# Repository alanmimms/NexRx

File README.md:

# NexRx: Open-Source Ham Radio SDR Receiver System
## Overview & Core Concepts

### What is NexRx?

NexRx is an ambitious open-source project that reimagines how we
interact with ham radio receivers. Instead of the knobs, buttons,
and menu diving that have defined radio interfaces for decades, NexRx
presents a browser-based interface built around a revolutionary
concept called "setboxes."

Think of it as bringing ham radio into the modern computing age -
where your radio's interface is as flexible and powerful as the
software on your computer, but still maintains the real-time
performance demands of RF communication.

This is an overview of the project. There is much more in the `./doc`
directory.

The entire project uses the MIT License, covering everything from
hardware designs and PCB layouts to software source code. This isn't
just another commercial radio with a fancy display - it's a
community-driven platform designed to push ham radio technology
forward for everyone.

### The Big Idea: Setboxes

Here's where NexRx gets interesting. Traditional radios force you to
think in terms of physical controls - turn this knob for frequency,
press that button for mode, flip this switch for antenna selection.
But why should software-defined radio be limited by the metaphors of
analog hardware?

NexRx introduces "setboxes" - think of them as smart presets that can
inherit settings from each other, just like object-oriented
programming. Instead of having separate "band" and "mode" controls,
you might have a setbox called "40m-CW-Contest" that inherits basic
40-meter settings from a parent "40m" setbox, adds CW-specific
parameters from a "CW" setbox, and then layers on contest-specific
configurations.

```mermaid
graph TD
    A[Global Settings] --> B[40m Band]
    A --> C[CW Mode]
    A --> D[Contest Setup]
    B --> E[40m-CW-Contest]
    C --> E
    D --> E
    
    style A fill:#e1f5fe
    style E fill:#c8e6c9
```

This hierarchy means you can set your antenna preferences once in
"Global Settings," define band-specific power levels in "40m Band,"
configure CW tone preferences in "CW Mode," and create
contest-specific memory channels in "Contest Setup." When you activate
"40m-CW-Contest," it automatically combines all these inherited
settings with any overrides you've defined specifically for that
configuration.

### Why This Matters

Traditional radio interfaces suffer from what we might call "control
soup" - every setting lives at the same level, making it hard to
organize your preferences logically. Want to use different antennas
for 160m versus other bands? You'll be manually switching antennas
every time you change bands. Prefer different power levels for CW
versus SSB? Hope you remember to adjust that knob every time you
change modes.

Setboxes solve this by letting you organize your radio's behavior
hierarchically. Set up your preferences once, then let the inheritance
system handle the details. The result is a radio that adapts to your
operating style instead of forcing you to adapt to its limitations.

### System Overview

NexRx consists of three main components that work together
seamlessly:

**Hardware Platform**: Built around an STM32H753 microcontroller
running at 480MHz with a full megabyte each of flash and RAM. This
isn't your typical Arduino project - we're talking serious
computational power running Zephyr RTOS. The RF hardware handles general
HF coverage from 1MHz to 30MHz.

**Embedded Software**: Written in modern C++20, this handles the
real-time RF control, basic DSP processing, and serves as a web
server. It presents itself to your computer as USB, so there's no
driver installation or network configuration hassles.

**Native Application**: This is where the magic happens. Using a
modern framework (TBD) this app runs on Linux, MacOS, and even Windows
on 64-bit PC or ARM. It handles advanced DSP, the setbox management
system, and provides rich visualizations like waterfall displays and
spectrum analysis. The interface runs entirely on the PC. The NexRx
hardware is essentially "headless".

The beauty of this architecture is its simplicity from the user's
perspective. Plug in the USB cable, install the app, and you're ready
to operate. But under the hood, you have access to computational power
and interface flexibility that would be impossible with traditional
radio architectures.

### Key Design Principles

**Inheritance Over Configuration**: Rather than configuring every
parameter for every situation, set up logical hierarchies and let
inheritance handle the complexity. Your "DX" setbox can inherit from
your "20m" setbox, which inherits from your "HF" setbox, which
inherits from your global preferences.

**Native Interface**: No drivers to manage, no compatibility worries
across different operating systems.

**Community-Driven Development**: The entire project is open source
with permissive licensing specifically to encourage community
contributions, modifications, and improvements. This is ham radio,
after all - we're supposed to be experimenting and learning.

**Real-Time Performance**: Despite the web-based interface, NexRx
maintains the real-time performance requirements of RF operation
through careful architecture and efficient protocols.

### The Vision

NexRx isn't just another SDR project - it's an attempt to demonstrate
what ham radio interfaces could become if we stopped thinking in terms
of analog radio metaphors and started thinking in terms of modern
software design patterns.

Imagine having complete recordings of every QSO with automatic digital
mode decoding, multiple simultaneous receive frequencies with
independent waterfalls, or antenna switching that automatically adapts
to your operating patterns. These capabilities become natural
extensions of the setbox paradigm rather than complex features bolted
onto traditional radio designs.

The goal is to create a platform that grows with you as an operator,
adapts to your preferences, and provides the kind of deep
configurability that makes ham radio uniquely satisfying - but without
the traditional complexity that makes advanced features intimidating
to explore.

# MCP Server

To create the Gemini MCP server I use for Kicad collaboration, you
have to add something like the following to your
`~/.gemini/settings.json` file:

	{

	...

	  "mcpServers": {
		"NexRxMCP": {
		  "command": "/home/yourusername/NexRx/.venv/bin/python3",
		  "args": ["/home/yourusername/NexRx/tools/mcp-server.py"],
		  "trust": true
		}
	  }
	}

# Building the gateware, firmware, and software

To do a top-level single-command build run `./build.sh` (or `cmake -B
build && cmake --build build`). This orchestrates all components and
generates the complete tree in build/:

  * `zephyr.bin`
  * `top.bin`
  * `build/app/nexrx-app`
  * `build/twin/nexrx-signalgen`

To iterate on a given subdirectory, you can repeatedly build just that
subdirectory's components by `cd` *subdir* `&& ./build.sh`.

  * `cd fw && ./build.sh` -> outputs to `fw/build/zephyr/`
  * `cd CPLD && ./build.sh` -> outputs to `CPLD/build/`
  * `cd app && ./build.sh` -> outputs to `app/build/`
  * `cd twin && ./build.sh` -> outputs to `twin/build/`

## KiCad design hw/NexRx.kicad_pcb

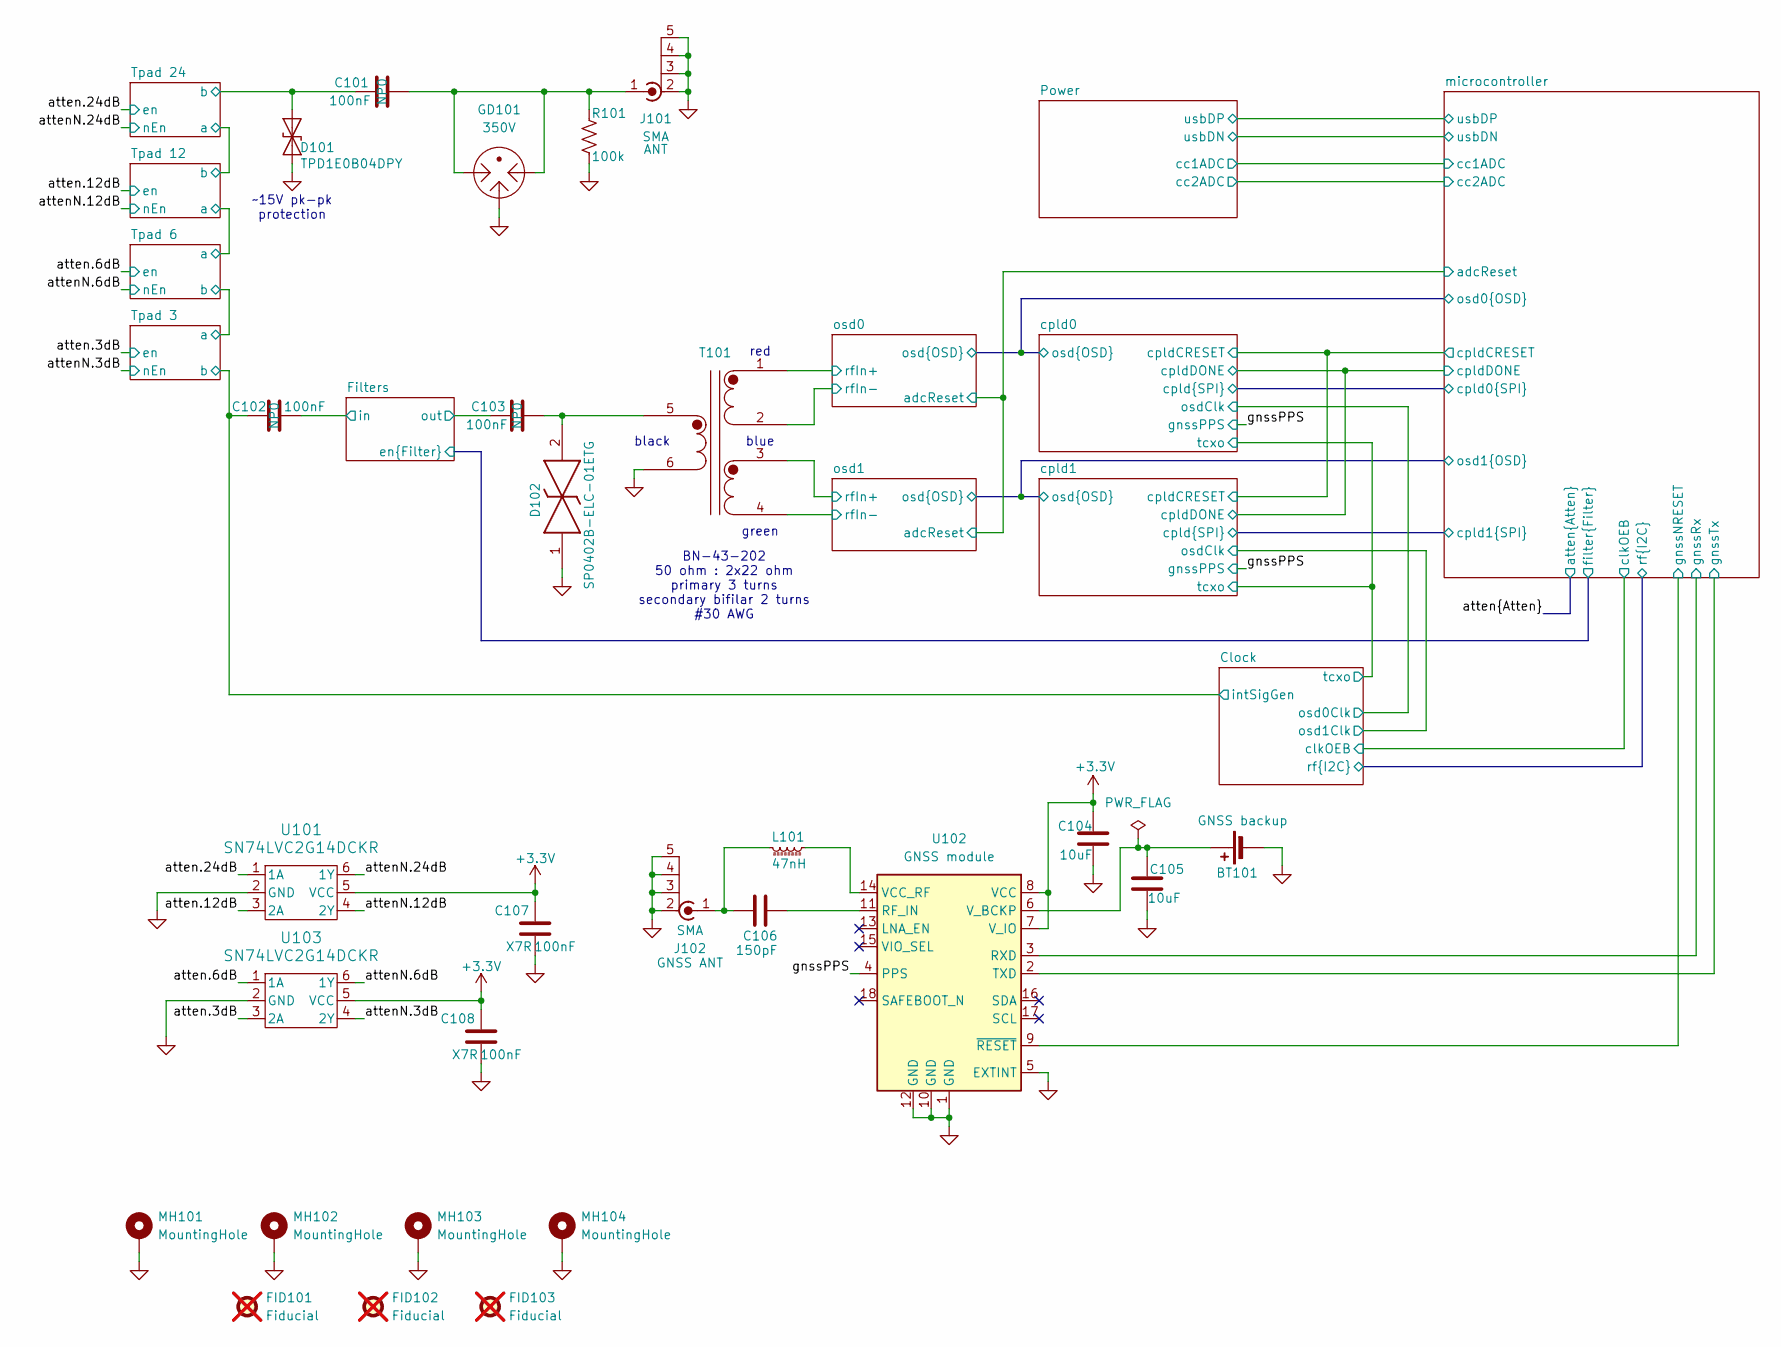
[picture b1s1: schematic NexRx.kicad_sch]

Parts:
BT101: CR3032 holder; CR2032_flat_holder-KH-CR2032-2-1; Mouser Part Number 855-S8401-46; LCSC C48687404
C101, C102, C103: 100nF; C_1206_3216Metric; MPN GRM3195C2A104JA01D; LCSC_PN C170182
C104, C105: 10uF; C_0402_1005Metric; MPN CL05A106MP6NUN8; LCSC C479655
C106: 150pF; C_0402_1005Metric; MPN C0402C151J3GACTU; Mouser Part Number C0402C151J3GACTU
C107, C108: 100nF; C_0402_1005Metric; MPN GCM155R71H104KE02D; LCSC_PN C307331
D101: TPD1E0B04DPY; D_0402_1005Metric; LCSC_PN C5182093
D102: SP0402B-ELC-01ETG; D_0402_1005Metric; MPN SP0402B-ELC-01ETG; LCSC_PN C1974049
FID101, FID102, FID103: Fiducial; Fiducial_0.5mm_Mask2mm; MPN n/a; Mouser Part Number n/a; not fitted
GD101: 350V; GDT3535S1RP; MPN GDT35-35-S1-RP; LCSC_PN C19947197
J101, J102: SMA; SMAJPHRATH1; MPN SMA-J-P-H-RA-TH1; LCSC_PN C493445
L101: 47nH; L_0603_1608Metric; MPN AIMC-0603-47NJ-T; LCSC C98076
MH101, MH102, MH103, MH104: MountingHole; MountingHole_3.2mm_M3_ISO7380_Pad
R101: 100k; R_0402_1005Metric; MPN RP0402BRD07100KL; LCSC_PN C25741
T101: BN-43-202, 50:2x22 ohm, 3 turns primary, 2 turns 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; Transformer-2P-2S-BN-43-202
U101, U103: SN74LVC2G14DCKR; SOIC_G14DCK3_TEX; LCSC_PN C37361
U102: GNSS module; MAXM10M20B; MPN ATGM336H-5N31; LCSC C90770

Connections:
+3.3V: C104.1, C107.1, C108.1, U101.5 (VCC), U102.7 (V_IO), U102.8 (VCC), U103.5 (VCC); also elsewhere on the board
/Clock/intSigGen: C102.2; also elsewhere on the board
/Filters/in: C102.1; also elsewhere on the board
/Filters/out: C103.1; also elsewhere on the board
/Tpad 24/b: C101.1, D101.1 (A1); also elsewhere on the board
/atten.3dB: U103.3 (2A); also elsewhere on the board
/atten.6dB: U103.1 (1A); also elsewhere on the board
/atten.12dB: U101.3 (2A); also elsewhere on the board
/atten.24dB: U101.1 (1A); also elsewhere on the board
/attenN.3dB: U103.4 (2Y); also elsewhere on the board
/attenN.6dB: U103.6 (1Y); also elsewhere on the board
/attenN.12dB: U101.4 (2Y); also elsewhere on the board
/attenN.24dB: U101.6 (1Y); also elsewhere on the board
/gnssPPS: U102.4 (PPS); also elsewhere on the board
/microcontroller/gnssNRESET: U102.9 (~RESET); also elsewhere on the board
/microcontroller/gnssRx: U102.3 (RXD); also elsewhere on the board
/microcontroller/gnssTx: U102.2 (TXD); also elsewhere on the board
/osd0/rfIn+: T101.1 (S1A); also elsewhere on the board
/osd0/rfIn-: T101.2 (S1B); also elsewhere on the board
/osd1/rfIn+: T101.3 (S2A); also elsewhere on the board
/osd1/rfIn-: T101.4 (S2B); also elsewhere on the board
GND: BT101.2 (-), C104.2, C105.1, C107.2, C108.2, D101.2 (A2), D102.1, GD101.2, J101.2 (Ext), J101.3 (Ext), J101.4 (Ext), J101.5 (Ext), J102.2 (Ext), J102.3 (Ext), J102.4 (Ext), J102.5 (Ext), MH101.1, MH102.1, MH103.1, MH104.1, R101.2, T101.6 (P1B), U101.2 (GND), U102.1 (GND), U102.5 (EXTINT), U102.10 (GND), U102.12 (GND), U103.2 (GND); also elsewhere on the board
unnamed: BT101.1 (+), C105.2, U102.6 (V_BCKP)
unnamed: C101.2, GD101.1, GD101.3, J101.1 (In), R101.1
unnamed: C106.2, J102.1 (In), L101.2
unnamed: C103.2, D102.2, T101.5 (P1A)
unnamed: C106.1, U102.11 (RF_IN)
unnamed: L101.1, U102.14 (VCC_RF)

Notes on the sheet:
black
red
blue
green
~15V pk-pk protection
BN-43-202 50 ohm : 2x22 ohm primary 3 turns secondary bifilar 2 turns #30 AWG

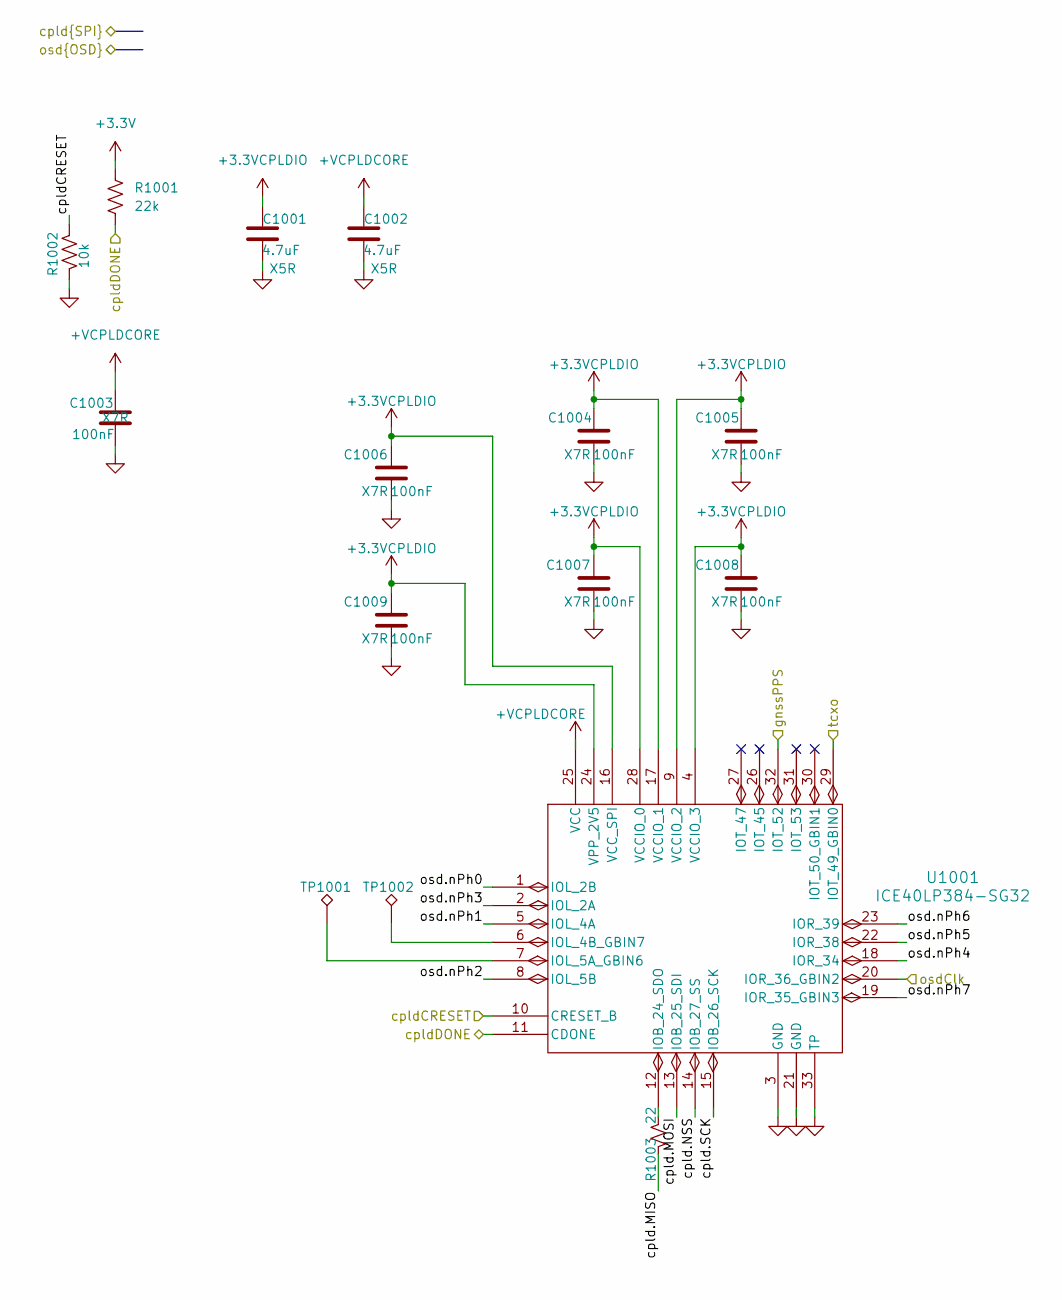
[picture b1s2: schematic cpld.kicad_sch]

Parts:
C1001, C1002: 4.7uF; C_0402_1005Metric; MPN CM05X5R475M10AH; LCSC_PN C23733
C1003, C1004, C1005, C1006, C1007, C1008, C1009: 100nF; C_0402_1005Metric; MPN GCM155R71H104KE02D; LCSC_PN C307331
R1001: 22k; R_0402_1005Metric; LCSC_PN C25768
R1002: 10k; R_0402_1005Metric; MPN RT0402BRD0710KL; JLCPCBpn C728576
R1003: 22; R_0402_1005Metric; MPN 560112110216; JLCPCBpn C4258780
TP1001, TP1002: TestPoint_Alt; TestPoint_Pad_1.0x1.0mm
U1001: ICE40LP384-SG32; QFNS32_LAT; MPN ICE40LP384-SG32; Mouser Part Number 842-ICE40LP384SG32

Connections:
+3.3V: C1001.1, C1004.1, C1005.1, C1006.1, C1007.1, C1008.1, C1009.1, R1001.1, U1001.4 (VCCIO_3), U1001.9 (VCCIO_2), U1001.16 (VCC_SPI), U1001.17 (VCCIO_1), U1001.24 (VPP_2V5), U1001.28 (VCCIO_0); also elsewhere on the board
+VCPLDCORE: C1002.1, C1003.2, U1001.25 (VCC); also elsewhere on the board
/Clock/osd1Clk: U1001.20 (IOR_36_GBIN2); also elsewhere on the board
/Clock/tcxo: U1001.29 (IOT_49_GBIN0); also elsewhere on the board
/cpld0/cpldCRESET: R1002.1, U1001.10 (CRESET_B); also elsewhere on the board
/cpld0/cpldDONE: R1001.2, U1001.11 (CDONE); also elsewhere on the board
/cpld1/cpld.MISO: R1003.2; also elsewhere on the board
/cpld1/cpld.MOSI: U1001.13 (IOB_25_SDI); also elsewhere on the board
/cpld1/cpld.NSS: U1001.14 (IOB_27_SS); also elsewhere on the board
/cpld1/cpld.SCK: U1001.15 (IOB_26_SCK); also elsewhere on the board
/cpld1/osd.nPh0: U1001.1 (IOL_2B); also elsewhere on the board
/cpld1/osd.nPh1: U1001.5 (IOL_4A); also elsewhere on the board
/cpld1/osd.nPh2: U1001.8 (IOL_5B); also elsewhere on the board
/cpld1/osd.nPh3: U1001.2 (IOL_2A); also elsewhere on the board
/cpld1/osd.nPh4: U1001.18 (IOR_34); also elsewhere on the board
/cpld1/osd.nPh5: U1001.22 (IOR_38); also elsewhere on the board
/cpld1/osd.nPh6: U1001.23 (IOR_39); also elsewhere on the board
/cpld1/osd.nPh7: U1001.19 (IOR_35_GBIN3); also elsewhere on the board
/gnssPPS: U1001.32 (IOT_52); also elsewhere on the board
GND: C1001.2, C1002.2, C1003.1, C1004.2, C1005.2, C1006.2, C1007.2, C1008.2, C1009.2, R1002.2, U1001.3 (GND), U1001.21 (GND), U1001.33 (TP); also elsewhere on the board
unnamed: R1003.1, U1001.12 (IOB_24_SDO)
unnamed: TP1002.1, U1001.6 (IOL_4B_GBIN7)
unnamed: TP1001.1, U1001.7 (IOL_5A_GBIN6)

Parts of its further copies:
C1401, C1402: 4.7uF; C_0402_1005Metric; MPN CM05X5R475M10AH; LCSC_PN C23733
C1403, C1404, C1405, C1406, C1407, C1408, C1409: 100nF; C_0402_1005Metric; MPN GCM155R71H104KE02D; LCSC_PN C307331
R1401: 22k; R_0402_1005Metric; LCSC_PN C25768
R1402: 10k; R_0402_1005Metric; MPN RT0402BRD0710KL; JLCPCBpn C728576
R1403: 22; R_0402_1005Metric; MPN 560112110216; JLCPCBpn C4258780
TP1401, TP1402: TestPoint_Alt; TestPoint_Pad_1.0x1.0mm
U1401: ICE40LP384-SG32; QFNS32_LAT; MPN ICE40LP384-SG32; Mouser Part Number 842-ICE40LP384SG32

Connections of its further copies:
+3.3V: C1401.1, C1404.1, C1405.1, C1406.1, C1407.1, C1408.1, C1409.1, R1401.1, U1401.4 (VCCIO_3), U1401.9 (VCCIO_2), U1401.16 (VCC_SPI), U1401.17 (VCCIO_1), U1401.24 (VPP_2V5), U1401.28 (VCCIO_0); also elsewhere on the board
+VCPLDCORE: C1402.1, C1403.2, U1401.25 (VCC); also elsewhere on the board
/Clock/osd0Clk: U1401.20 (IOR_36_GBIN2); also elsewhere on the board
/Clock/tcxo: U1401.29 (IOT_49_GBIN0); also elsewhere on the board
/cpld0/cpld.NSS: U1401.14 (IOB_27_SS); also elsewhere on the board
/cpld0/cpldCRESET: R1402.1, U1401.10 (CRESET_B); also elsewhere on the board
/cpld0/cpldDONE: R1401.2, U1401.11 (CDONE); also elsewhere on the board
/cpld0/osd.nPh0: U1401.1 (IOL_2B); also elsewhere on the board
/cpld0/osd.nPh1: U1401.5 (IOL_4A); also elsewhere on the board
/cpld0/osd.nPh2: U1401.8 (IOL_5B); also elsewhere on the board
/cpld0/osd.nPh3: U1401.2 (IOL_2A); also elsewhere on the board
/cpld0/osd.nPh4: U1401.18 (IOR_34); also elsewhere on the board
/cpld0/osd.nPh5: U1401.22 (IOR_38); also elsewhere on the board
/cpld0/osd.nPh6: U1401.23 (IOR_39); also elsewhere on the board
/cpld0/osd.nPh7: U1401.19 (IOR_35_GBIN3); also elsewhere on the board
/cpld1/cpld.MISO: R1403.2; also elsewhere on the board
/cpld1/cpld.MOSI: U1401.13 (IOB_25_SDI); also elsewhere on the board
/cpld1/cpld.SCK: U1401.15 (IOB_26_SCK); also elsewhere on the board
/gnssPPS: U1401.32 (IOT_52); also elsewhere on the board
GND: C1401.2, C1402.2, C1403.1, C1404.2, C1405.2, C1406.2, C1407.2, C1408.2, C1409.2, R1402.2, U1401.3 (GND), U1401.21 (GND), U1401.33 (TP); also elsewhere on the board
unnamed: R1403.1, U1401.12 (IOB_24_SDO)
unnamed: TP1402.1, U1401.6 (IOL_4B_GBIN7)
unnamed: TP1401.1, U1401.7 (IOL_5A_GBIN6)

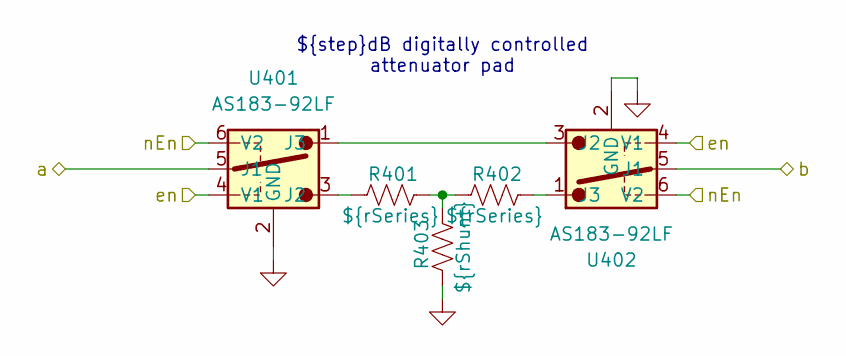
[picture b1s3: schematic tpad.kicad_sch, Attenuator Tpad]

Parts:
R401, R402: ${rSeries}; R_0402_1005Metric; LCSC_PN ${rSeriesLCSC}
R403: ${rShunt}; R_0402_1005Metric; LCSC_PN C270643
U401, U402: AS183-92LF; SOT65P220X110-6N; MPN AS183-92LF; LCSC_PN C2654768

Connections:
/Clock/intSigGen: U402.5 (J1); also elsewhere on the board
/Tpad 3/a: U401.5 (J1); also elsewhere on the board
/atten.3dB: U401.4 (V1), U402.4 (V1); also elsewhere on the board
/attenN.3dB: U401.6 (V2), U402.6 (V2); also elsewhere on the board
GND: R403.2, U401.2 (GND), U402.2 (GND); also elsewhere on the board
unnamed: R401.1, R402.2, R403.1
unnamed: R401.2, U401.3 (J2)
unnamed: U401.1 (J3), U402.3 (J2)
unnamed: R402.1, U402.1 (J3)

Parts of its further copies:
U501, U502, U601, U602, U701, U702: AS183-92LF; SOT65P220X110-6N; MPN AS183-92LF; LCSC_PN C2654768

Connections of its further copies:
/Tpad 3/a: U502.5 (J1); also elsewhere on the board
/Tpad 12/a: U501.5 (J1), U601.5 (J1)
/Tpad 12/b: U602.5 (J1), U701.5 (J1)
/Tpad 24/b: U702.5 (J1); also elsewhere on the board
/atten.6dB: U501.4 (V1), U502.4 (V1); also elsewhere on the board
/atten.12dB: U601.4 (V1), U602.4 (V1); also elsewhere on the board
/atten.24dB: U701.4 (V1), U702.4 (V1); also elsewhere on the board
/attenN.6dB: U501.6 (V2), U502.6 (V2); also elsewhere on the board
/attenN.12dB: U601.6 (V2), U602.6 (V2); also elsewhere on the board
/attenN.24dB: U701.6 (V2), U702.6 (V2); also elsewhere on the board
GND: U501.2 (GND), U502.2 (GND), U601.2 (GND), U602.2 (GND), U701.2 (GND), U702.2 (GND); also elsewhere on the board
unnamed 214: U501.3 (J2); also elsewhere on the board
unnamed: U501.1 (J3), U502.3 (J2)
unnamed 216: U502.1 (J3); also elsewhere on the board
unnamed 217: U601.3 (J2); also elsewhere on the board
unnamed: U601.1 (J3), U602.3 (J2)
unnamed 219: U602.1 (J3); also elsewhere on the board
unnamed 220: U701.3 (J2); also elsewhere on the board
unnamed: U701.1 (J3), U702.3 (J2)
unnamed 222: U702.1 (J3); also elsewhere on the board

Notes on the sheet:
${step}dB digitally controlled attenuator pad

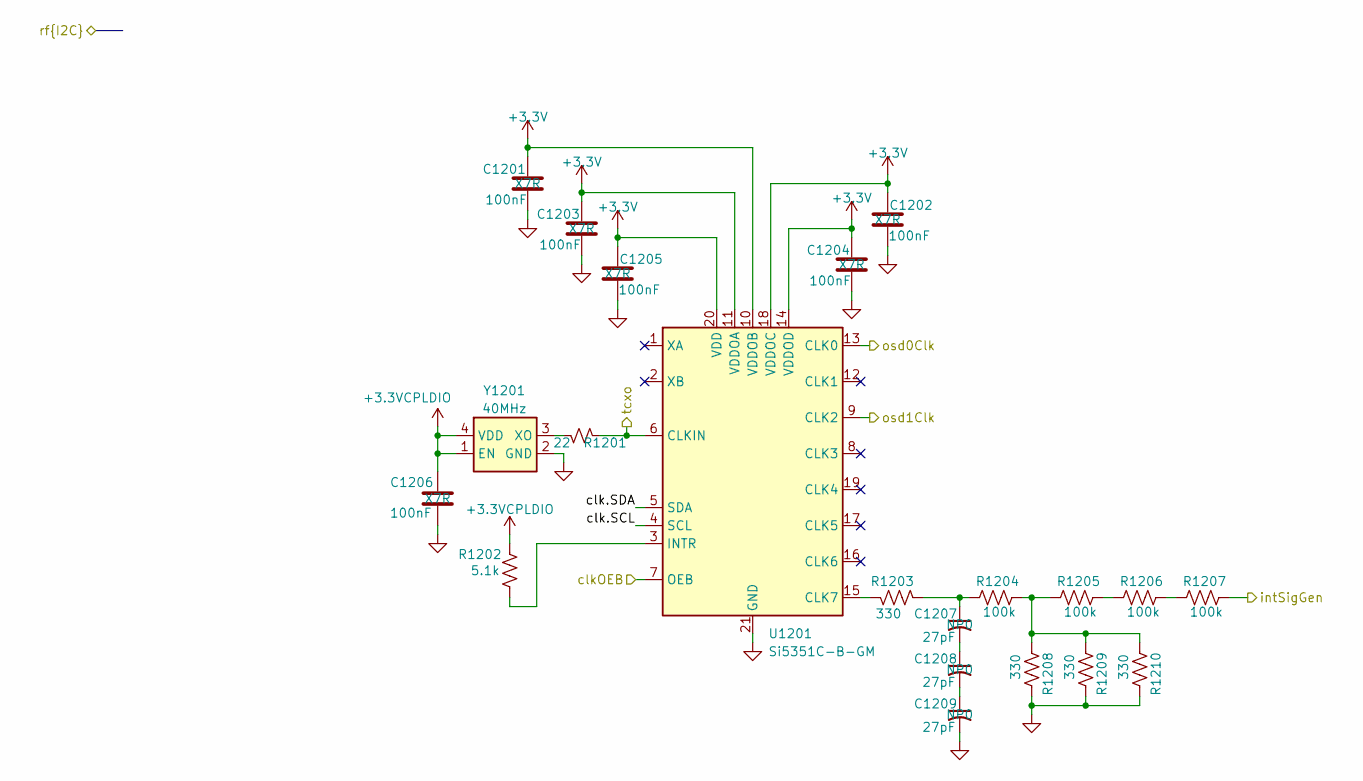
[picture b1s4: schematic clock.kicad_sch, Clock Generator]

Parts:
C1201, C1202, C1203, C1204, C1205, C1206: 100nF; C_0402_1005Metric; MPN GCM155R71H104KE02D; LCSC_PN C307331
C1207, C1208, C1209: 27pF; C_0402_1005Metric; MPN 04023A270JAT2A; Mouser Part Number 581-04023A270JAT2A
R1201: 22; R_0402_1005Metric; MPN 560112110216; JLCPCBpn C4258780
R1202: 5.1k; R_0402_1005Metric; MPN AC0402FR-7W5K1L; LCSC_PN C854378
R1203: 330; R_0402_1005Metric; MPN RC0402JR-7D330RL; LCSC_PN C25104
R1204, R1206, R1207: 100k; R_0402_1005Metric; MPN RP0402BRD07100KL; JLCPCBpn C728576
R1205: 100k; R_0402_1005Metric; MPN RP0402BRD07100KL; LCSC_PN C25741
R1208, R1209, R1210: 330; R_0402_1005Metric; MPN RC0402JR-7D330RL; JLCPCBpn C854274
U1201: Si5351C-B-GM; QFN-20-1EP_4x4mm_P0.5mm_EP2.7x2.7mm; MPN SI5351C-B-GM; Mouser Part Number 634-SI5351C-B-GM
Y1201: 40MHz; ECSTXO201633400TR; MPN ECS-TXO-2016-33-400-TR; LCSC_PN C2451471

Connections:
+3.3V: C1201.2, C1202.2, C1203.2, C1204.2, C1205.2, C1206.1, R1202.1, U1201.10 (VDDOB), U1201.11 (VDDOA), U1201.14 (VDDOD), U1201.18 (VDDOC), U1201.20 (VDD), Y1201.1 (EN), Y1201.4 (VDD); also elsewhere on the board
/Clock/clk.SCL: U1201.4 (SCL)
/Clock/clk.SDA: U1201.5 (SDA)
/Clock/clkOEB: U1201.7 (OEB); also elsewhere on the board
/Clock/intSigGen: R1207.2; also elsewhere on the board
/Clock/osd0Clk: U1201.13 (CLK0); also elsewhere on the board
/Clock/osd1Clk: U1201.9 (CLK2); also elsewhere on the board
/Clock/tcxo: R1201.2, U1201.6 (CLKIN); also elsewhere on the board
GND: C1201.1, C1202.1, C1203.1, C1204.1, C1205.1, C1206.2, C1209.2, R1208.1, R1209.1, R1210.1, U1201.21 (GND), Y1201.2 (GND); also elsewhere on the board
unnamed: C1207.1, R1203.2, R1204.1
unnamed: C1207.2, C1208.1
unnamed: C1208.2, C1209.1
unnamed: R1204.2, R1205.1, R1208.2, R1209.2, R1210.2
unnamed: R1205.2, R1206.1
unnamed: R1206.2, R1207.1
unnamed: R1203.1, U1201.15 (CLK7)
unnamed: R1202.2, U1201.3 (INTR)
unnamed: R1201.1, Y1201.3 (XO)

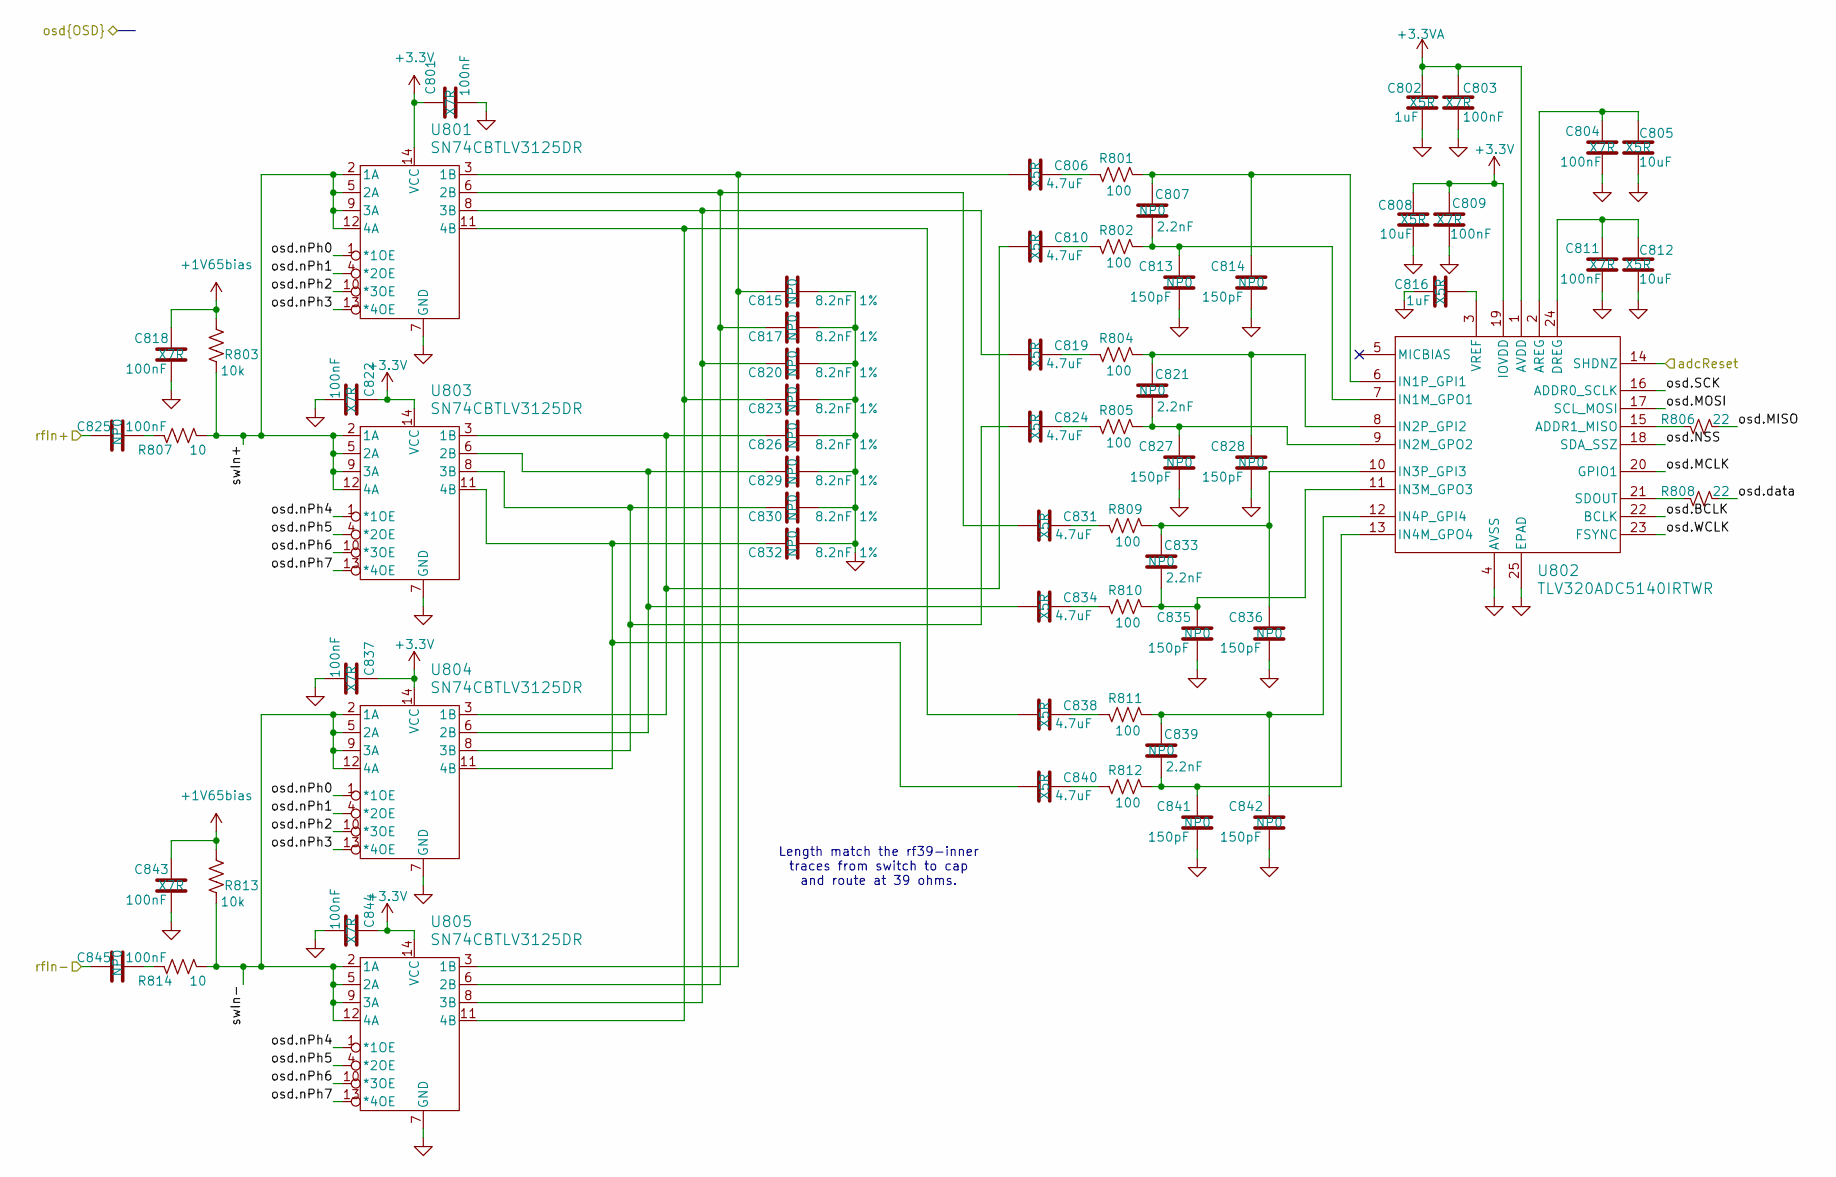
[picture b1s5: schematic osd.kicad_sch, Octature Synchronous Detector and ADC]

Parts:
C801, C803, C804, C809, C811, C818, C822, C837, C843, C844: 100nF; C_0402_1005Metric; MPN GCM155R71H104KE02D; LCSC_PN C307331
C802, C816: 1uF; C_0402_1005Metric; MPN GRM155R61E105MA12D; LCSC_PN C77009
C805, C808, C812: 10uF; C_0402_1005Metric; MPN CL05A106MP6NUN8; LCSC_PN C76991
C806, C810, C819, C824, C831, C834, C838, C840: 4.7uF; C_0402_1005Metric; MPN CM05X5R475M10AH; LCSC_PN C23733
C807, C821, C833, C839: 2.2nF; C_0402_1005Metric; MPN C0402C222K3GECTU; LCSC_PN C2167434
C813, C814, C827, C828, C835, C836, C841, C842: 150pF; C_0402_1005Metric; MPN C0402C151J3GACTU; LCSC_PN C12220
C815, C817, C820, C823, C826, C829, C830, C832: 8.2nF 1%; C_0805_2012Metric; Mouser Part Number 581-08053A822FAT2A
C825, C845: 100nF; C_1206_3216Metric; MPN GRM3195C2A104JA01D; LCSC_PN C170182
R801, R802, R804, R805, R809, R810, R811, R812: 100; R_0402_1005Metric; MPN MCS04020C1000FE000; LCSC_PN C332259
R803, R813: 10k; R_0402_1005Metric; MPN RT0402BRD0710KL; LCSC_PN C283961
R806, R808: 22; R_0402_1005Metric; MPN 560112110216; JLCPCBpn C4258780
R807, R814: 10; R_0402_1005Metric; MPN RE0402FRE0710RL; LCSC_PN C25077
U801, U803, U804, U805: SN74CBTLV3125DR; DGV14; MPN SN74CBTLV3125DGVR; LCSC_PN C2674493
U802: TLV320ADC5140IRTWR; RTW24_4P15X4P15_TEX; MPN TLV320ADC5140IRTWR; Mouser Part Number 595-V320ADC5140IRTWR

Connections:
+1V65bias: C818.1, C843.1, R803.1, R813.1; also elsewhere on the board
+3.3V: C801.1, C808.1, C809.1, C822.1, C837.1, C844.1, U801.14 (VCC), U802.19 (IOVDD), U803.14 (VCC), U804.14 (VCC), U805.14 (VCC); also elsewhere on the board
+3.3VA: C802.2, C803.2, U802.1 (AVDD); also elsewhere on the board
/cpld0/osd.NSS: U802.18 (SDA_SSZ); also elsewhere on the board
/cpld0/osd.data: R808.1; also elsewhere on the board
/cpld0/osd.nPh0: U801.1 (*1OE), U804.1 (*1OE); also elsewhere on the board
/cpld0/osd.nPh1: U801.4 (*2OE), U804.4 (*2OE); also elsewhere on the board
/cpld0/osd.nPh2: U801.10 (*3OE), U804.10 (*3OE); also elsewhere on the board
/cpld0/osd.nPh3: U801.13 (*4OE), U804.13 (*4OE); also elsewhere on the board
/cpld0/osd.nPh4: U803.1 (*1OE), U805.1 (*1OE); also elsewhere on the board
/cpld0/osd.nPh5: U803.4 (*2OE), U805.4 (*2OE); also elsewhere on the board
/cpld0/osd.nPh6: U803.10 (*3OE), U805.10 (*3OE); also elsewhere on the board
/cpld0/osd.nPh7: U803.13 (*4OE), U805.13 (*4OE); also elsewhere on the board
/cpld1/osd.BCLK: U802.22 (BCLK); also elsewhere on the board
/cpld1/osd.MCLK: U802.20 (GPIO1); also elsewhere on the board
/cpld1/osd.MISO: R806.1; also elsewhere on the board
/cpld1/osd.MOSI: U802.17 (SCL_MOSI); also elsewhere on the board
/cpld1/osd.SCK: U802.16 (ADDR0_SCLK); also elsewhere on the board
/cpld1/osd.WCLK: U802.23 (FSYNC); also elsewhere on the board
/microcontroller/adcReset: U802.14 (SHDNZ); also elsewhere on the board
/osd0/rfIn+: C825.1; also elsewhere on the board
/osd0/rfIn-: C845.1; also elsewhere on the board
/osd0/swIn+: R803.2, R807.2, U801.2 (1A), U801.5 (2A), U801.9 (3A), U801.12 (4A), U803.2 (1A), U803.5 (2A), U803.9 (3A), U803.12 (4A)
/osd0/swIn-: R813.2, R814.2, U804.2 (1A), U804.5 (2A), U804.9 (3A), U804.12 (4A), U805.2 (1A), U805.5 (2A), U805.9 (3A), U805.12 (4A)
GND: C801.2, C802.1, C803.1, C804.2, C805.2, C808.2, C809.2, C811.2, C812.2, C813.2, C814.2, C815.2, C816.1, C817.2, C818.2, C820.2, C822.2, C823.2, C826.2, C827.2, C828.2, C829.2, C830.2, C832.2, C835.2, C836.2, C837.2, C841.2, C842.2, C843.2, C844.2, U801.7 (GND), U802.4 (AVSS), U802.25 (EPAD), U803.7 (GND), U804.7 (GND), U805.7 (GND); also elsewhere on the board
unnamed: C806.2, R801.1
unnamed: C810.2, R802.1
unnamed: C819.2, R804.1
unnamed: C824.2, R805.1
unnamed: C825.2, R807.1
unnamed: C831.2, R809.1
unnamed: C834.2, R810.1
unnamed: C838.2, R811.1
unnamed: C840.2, R812.1
unnamed: C845.2, R814.1
unnamed: C806.1, C815.1, U801.3 (1B), U805.3 (1B)
unnamed: C817.1, C831.1, U801.6 (2B), U805.6 (2B)
unnamed: C819.1, C820.1, U801.8 (3B), U805.8 (3B)
unnamed: C823.1, C838.1, U801.11 (4B), U805.11 (4B)
unnamed: R806.2, U802.15 (ADDR1_MISO)
unnamed: C804.1, C805.1, U802.2 (AREG)
unnamed: C811.1, C812.1, U802.24 (DREG)
unnamed: C807.2, C813.1, R802.2, U802.7 (IN1M_GPO1)
unnamed: C807.1, C814.1, R801.2, U802.6 (IN1P_GPI1)
unnamed: C821.2, C827.1, R805.2, U802.9 (IN2M_GPO2)
unnamed: C821.1, C828.1, R804.2, U802.8 (IN2P_GPI2)
unnamed: C833.2, C835.1, R810.2, U802.11 (IN3M_GPO3)
unnamed: C833.1, C836.1, R809.2, U802.10 (IN3P_GPI3)
unnamed: C839.2, C841.1, R812.2, U802.13 (IN4M_GPO4)
unnamed: C839.1, C842.1, R811.2, U802.12 (IN4P_GPI4)
unnamed: R808.2, U802.21 (SDOUT)
unnamed: C816.2, U802.3 (VREF)
unnamed: C810.1, C826.1, U803.3 (1B), U804.3 (1B)
unnamed: C829.1, C834.1, U803.6 (2B), U804.6 (2B)
unnamed: C824.1, C830.1, U803.8 (3B), U804.8 (3B)
unnamed: C832.1, C840.1, U803.11 (4B), U804.11 (4B)

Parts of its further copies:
C901, C903, C904, C909, C911, C918, C922, C937, C943, C944: 100nF; C_0402_1005Metric; MPN GCM155R71H104KE02D; LCSC_PN C307331
C902, C916: 1uF; C_0402_1005Metric; MPN GRM155R61E105MA12D; LCSC_PN C77009
C905, C908, C912: 10uF; C_0402_1005Metric; MPN CL05A106MP6NUN8; LCSC_PN C76991
C906, C910, C919, C924, C931, C934, C938, C940: 4.7uF; C_0402_1005Metric; MPN CM05X5R475M10AH; LCSC_PN C23733
C907, C921, C933, C939: 2.2nF; C_0402_1005Metric; MPN C0402C222K3GECTU; LCSC_PN C2167434
C913, C914, C927, C928, C935, C936, C941, C942: 150pF; C_0402_1005Metric; MPN C0402C151J3GACTU; LCSC_PN C12220
C915, C917, C920, C923, C926, C929, C930, C932: 8.2nF 1%; C_0805_2012Metric; Mouser Part Number 581-08053A822FAT2A
C925, C945: 100nF; C_1206_3216Metric; MPN GRM3195C2A104JA01D; LCSC_PN C170182
R901, R902, R904, R905, R909, R910, R911, R912: 100; R_0402_1005Metric; MPN MCS04020C1000FE000; LCSC_PN C332259
R903, R913: 10k; R_0402_1005Metric; MPN RT0402BRD0710KL; LCSC_PN C283961
R906, R908: 22; R_0402_1005Metric; MPN 560112110216; JLCPCBpn C4258780
R907, R914: 10; R_0402_1005Metric; MPN RE0402FRE0710RL; LCSC_PN C25077
U901, U903, U904, U905: SN74CBTLV3125DR; DGV14; MPN SN74CBTLV3125DGVR; LCSC_PN C2674493
U902: TLV320ADC5140IRTWR; RTW24_4P15X4P15_TEX; MPN TLV320ADC5140IRTWR; Mouser Part Number 595-V320ADC5140IRTWR

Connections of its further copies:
+1V65bias: C918.1, C943.1, R903.1, R913.1; also elsewhere on the board
+3.3V: C901.1, C908.1, C909.1, C922.1, C937.1, C944.1, U901.14 (VCC), U902.19 (IOVDD), U903.14 (VCC), U904.14 (VCC), U905.14 (VCC); also elsewhere on the board
+3.3VA: C902.2, C903.2, U902.1 (AVDD); also elsewhere on the board
/cpld1/osd.BCLK: U902.22 (BCLK); also elsewhere on the board
/cpld1/osd.MCLK: U902.20 (GPIO1); also elsewhere on the board
/cpld1/osd.MISO: R906.1; also elsewhere on the board
/cpld1/osd.MOSI: U902.17 (SCL_MOSI); also elsewhere on the board
/cpld1/osd.NSS: U902.18 (SDA_SSZ); also elsewhere on the board
/cpld1/osd.SCK: U902.16 (ADDR0_SCLK); also elsewhere on the board
/cpld1/osd.WCLK: U902.23 (FSYNC); also elsewhere on the board
/cpld1/osd.data: R908.1; also elsewhere on the board
/cpld1/osd.nPh0: U901.1 (*1OE), U904.1 (*1OE); also elsewhere on the board
/cpld1/osd.nPh1: U901.4 (*2OE), U904.4 (*2OE); also elsewhere on the board
/cpld1/osd.nPh2: U901.10 (*3OE), U904.10 (*3OE); also elsewhere on the board
/cpld1/osd.nPh3: U901.13 (*4OE), U904.13 (*4OE); also elsewhere on the board
/cpld1/osd.nPh4: U903.1 (*1OE), U905.1 (*1OE); also elsewhere on the board
/cpld1/osd.nPh5: U903.4 (*2OE), U905.4 (*2OE); also elsewhere on the board
/cpld1/osd.nPh6: U903.10 (*3OE), U905.10 (*3OE); also elsewhere on the board
/cpld1/osd.nPh7: U903.13 (*4OE), U905.13 (*4OE); also elsewhere on the board
/microcontroller/adcReset: U902.14 (SHDNZ); also elsewhere on the board
/osd1/rfIn+: C925.1; also elsewhere on the board
/osd1/rfIn-: C945.1; also elsewhere on the board
/osd1/swIn+: R903.2, R907.2, U901.2 (1A), U901.5 (2A), U901.9 (3A), U901.12 (4A), U903.2 (1A), U903.5 (2A), U903.9 (3A), U903.12 (4A)
/osd1/swIn-: R913.2, R914.2, U904.2 (1A), U904.5 (2A), U904.9 (3A), U904.12 (4A), U905.2 (1A), U905.5 (2A), U905.9 (3A), U905.12 (4A)
GND: C901.2, C902.1, C903.1, C904.2, C905.2, C908.2, C909.2, C911.2, C912.2, C913.2, C914.2, C915.2, C916.1, C917.2, C918.2, C920.2, C922.2, C923.2, C926.2, C927.2, C928.2, C929.2, C930.2, C932.2, C935.2, C936.2, C937.2, C941.2, C942.2, C943.2, C944.2, U901.7 (GND), U902.4 (AVSS), U902.25 (EPAD), U903.7 (GND), U904.7 (GND), U905.7 (GND); also elsewhere on the board
unnamed: C906.2, R901.1
unnamed: C910.2, R902.1
unnamed: C919.2, R904.1
unnamed: C924.2, R905.1
unnamed: C925.2, R907.1
unnamed: C931.2, R909.1
unnamed: C934.2, R910.1
unnamed: C938.2, R911.1
unnamed: C940.2, R912.1
unnamed: C945.2, R914.1
unnamed: C906.1, C915.1, U901.3 (1B), U905.3 (1B)
unnamed: C917.1, C931.1, U901.6 (2B), U905.6 (2B)
unnamed: C919.1, C920.1, U901.8 (3B), U905.8 (3B)
unnamed: C923.1, C938.1, U901.11 (4B), U905.11 (4B)
unnamed: R906.2, U902.15 (ADDR1_MISO)
unnamed: C904.1, C905.1, U902.2 (AREG)
unnamed: C911.1, C912.1, U902.24 (DREG)
unnamed: C907.2, C913.1, R902.2, U902.7 (IN1M_GPO1)
unnamed: C907.1, C914.1, R901.2, U902.6 (IN1P_GPI1)
unnamed: C921.2, C927.1, R905.2, U902.9 (IN2M_GPO2)
unnamed: C921.1, C928.1, R904.2, U902.8 (IN2P_GPI2)
unnamed: C933.2, C935.1, R910.2, U902.11 (IN3M_GPO3)
unnamed: C933.1, C936.1, R909.2, U902.10 (IN3P_GPI3)
unnamed: C939.2, C941.1, R912.2, U902.13 (IN4M_GPO4)
unnamed: C939.1, C942.1, R911.2, U902.12 (IN4P_GPI4)
unnamed: R908.2, U902.21 (SDOUT)
unnamed: C916.2, U902.3 (VREF)
unnamed: C910.1, C926.1, U903.3 (1B), U904.3 (1B)
unnamed: C929.1, C934.1, U903.6 (2B), U904.6 (2B)
unnamed: C924.1, C930.1, U903.8 (3B), U904.8 (3B)
unnamed: C932.1, C940.1, U903.11 (4B), U904.11 (4B)

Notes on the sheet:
Length match the rf39-inner traces from switch to cap and route at 39 ohms.
